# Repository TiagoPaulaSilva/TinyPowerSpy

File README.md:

# Tiny PowerSpy

Tiny PowerSpy is an IoT device, a smart plug for energy monitoring in wall outlets.

#### Compatible with: 
* [BitsTunnel](https://github.com/import-tiago/BitsTunnel)

## PCB Preview

## Enclosure Preview

## Schematic

### Contributing
0. Give this project a :star:
1. Create an issue and describe your idea.
2. [Fork it](https://github.com/import-tiago/TinyPowerSpy/fork).
3. Create your feature branch (`git checkout -b my-new-feature`).
4. Commit your changes (`git commit -a -m "Added feature title"`).
5. Publish the branch (`git push origin my-new-feature`).
6. Create a new pull request.
7. Done! :heavy_check_mark:

### License Information
<br /><span xmlns:dct="http://purl.org/dc/terms/" property="dct:title">Light's Thrill</span> by <a xmlns:cc="http://creativecommons.org/ns#" href="https://github.com/import-tiago" property="cc:attributionName" rel="cc:attributionURL">Tiago Silva</a> is licensed under a <a rel="license" href="http://creativecommons.org/licenses/by-sa/4.0/">Creative Commons Attribution-ShareAlike 4.0 International License</a>.<br />
Permissions beyond the scope of this license may be available at <a xmlns:cc="http://creativecommons.org/ns#" href="https://twitter.com/import_tiago" rel="cc:morePermissions">tiagodepaulasilva@gmail.com</a>.

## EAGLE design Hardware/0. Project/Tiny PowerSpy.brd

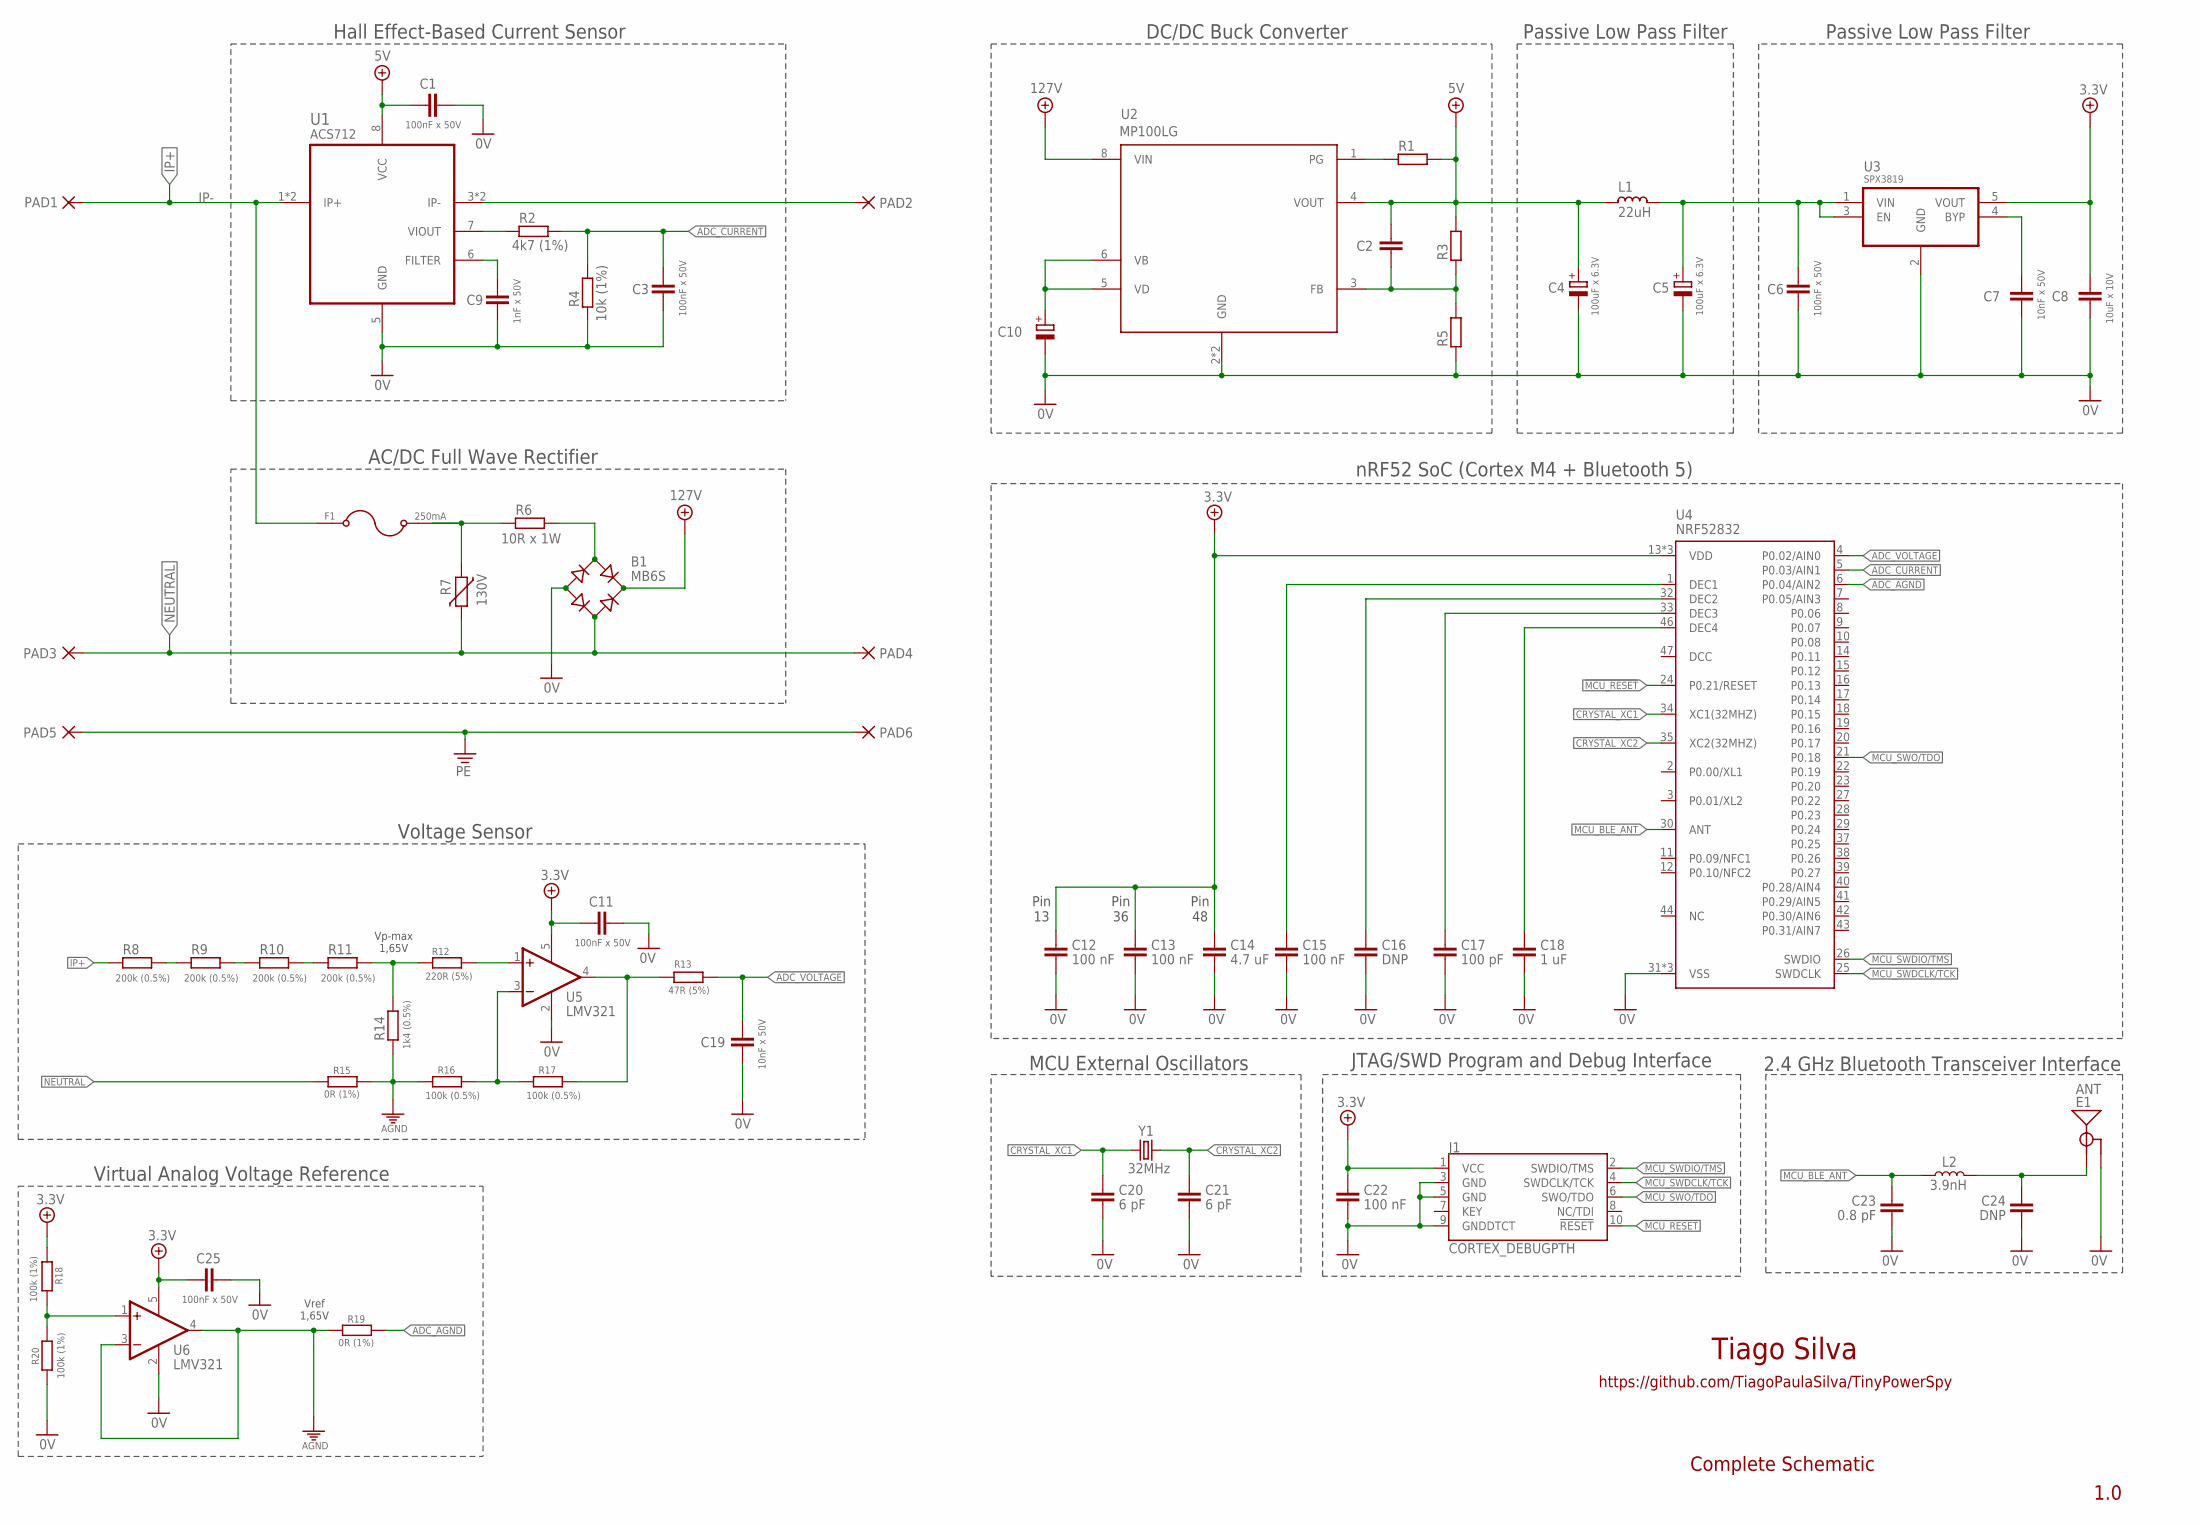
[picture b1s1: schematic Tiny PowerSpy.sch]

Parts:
B1: MB6S; SOIC-4
C1, C3, C6, C11, C25: 100nF x 50V; C0603
C2: C-EUC0603; C0603
C4, C5: 100uF x 6.3V; C1206K
C7, C19: 10nF x 50V; C0603
C8: 10uF x 10V; C0603
C9: 1nF x 50V; C0603
C10: CPOL-EUE3.5-8; E3,5-8
C12, C13, C15: 100 nF; C0402
C14: 4.7 uF; C0603
C16: DNP; C0402
C17: 100 pF; C0402
C18: 1 uF; C0603
C20, C21: 6 pF; C0402
C22: 100 nF; C0603
C23: 0.8 pF; C0603
C24: DNP; C0603
E1: ANT; TRACE_ANTENNA_2.4GHZ_15.2MM
F1: 250mA; FUSE_0154004.DR
J1: CORTEX_DEBUGPTH; 2X5-PTH-1.27MM
L1: 22uH; L0603
L2: 3.9nH; 0402
PAD1, PAD2, PAD4, PAD6: SMD5; SMD2,54-5,08
PAD3, PAD5: SMD2; SMD1,27-2,54
R1, R3, R5: R-EU_R0603; R0603
R2: 4k7 (1%); R0603
R4: 10k (1%); R0603
R6: 10R x 1W; 0207/5V
R7: 130V; S05K11
R8, R9, R10, R11: 200k (0.5%); R0603
R12: 220R (5%); R0603
R13: 47R (5%); R0603
R14: 1k4 (0.5%); R0603
R15, R19: 0R (1%); R0603
R16, R17: 100k (0.5%); R0603
R18, R20: 100k (1%); R0603
U1: ACS712; SOIC127P600X175-8N
U2: MP100LG; SOIC8E
U3: SPX3819; SOT95P280X145-5N
U4: NRF52832; QFN48-6X6MM
U5, U6: LMV321; SOT23-5
Y1: 32MHz; CRYSTAL-SMD-2.0X1.6MM

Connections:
0V: B1.-, C1.1, C3.2, C4.2, C5.2, C6.2, C7.2, C8.2, C9.2, C10.-, C11.1, C12.2, C13.2, C14.2, C15.2, C16.2, C17.2, C18.2, C19.2, C20.2, C21.2, C22.2, C23.2, C24.2, C25.2, E1.GND, J1.3 (GND), J1.5 (GND), J1.9 (GNDDTCT), R4.2, R5.1, R20.2, U1.5 (GND), U2.2 (GND), U2.9 (GND), U3.2 (GND), U4.31 (VSS), U4.45 (VSS), U4.EP (VSS), U5.2 (V-), U6.2 (V-)
3.3V: C8.1, C11.2, C12.1, C13.1, C14.1, C22.1, C25.1, J1.1 (VCC), R18.2, U3.5 (VOUT), U4.13 (VDD), U4.36 (VDD), U4.48 (VDD), U5.5 (V+), U6.5 (V+)
5V: C1.2, C2.1, C4.1, L1.2, R1.2, R3.2, U1.8 (VCC), U2.4 (VOUT)
127V: B1.+, U2.8 (VIN)
!MCU_RESET!: J1.10 (!RESET), U4.24 (P0.21/RESET)
ADC_AGND: R19.2, U4.6 (P0.04/AIN2)
ADC_CURRENT: C3.1, R2.2, R4.1, U4.5 (P0.03/AIN1)
ADC_VOLTAGE: C19.1, R13.1, U4.4 (P0.02/AIN0)
AGND: R14.2, R15.2, R16.2, R19.1, U6.3 (-IN), U6.4 (OUT)
CRYSTAL_XC1: C20.1, U4.34 (XC1(32MHZ)), Y1.3 (2)
CRYSTAL_XC2: C21.1, U4.35 (XC2(32MHZ)), Y1.1
IP+: F1.1, PAD1.1, R8.1, U1.1 (IP+), U1.2 (IP+)
IP-: PAD2.1, U1.3 (IP-), U1.4 (IP-)
MCU_BLE_ANT: C23.1, L2.2, U4.30 (ANT)
MCU_SWDCLK/TCK: J1.4 (SWDCLK/TCK), U4.25 (SWDCLK)
MCU_SWDIO/TMS: J1.2 (SWDIO/TMS), U4.26 (SWDIO)
MCU_SWO/TDO: J1.6 (SWO/TDO), U4.21 (P0.18)
unnamed: R1.1, U2.1 (PG)
unnamed: F1.2, R6.1, R7.1
unnamed: C16.1, U4.32 (DEC2)
unnamed: C2.2, R3.1, R5.2, U2.3 (FB)
unnamed: C10.+, U2.5 (VD), U2.6 (VB)
unnamed: C9.1, U1.6 (FILTER)
unnamed: B1.~1 (AC1), R6.2
unnamed: C15.1, U4.1 (DEC1)
unnamed: C18.1, U4.46 (DEC4)
unnamed: R2.1, U1.7 (VIOUT)
unnamed: C24.1, E1.ANT (SIGNAL), L2.1
unnamed: R9.2, R10.1
unnamed: C17.1, U4.33 (DEC3)
unnamed: R10.2, R11.1
unnamed: R13.2, R17.1, U5.4 (OUT)
unnamed: C5.1, C6.1, L1.1, U3.1 (VIN), U3.3 (EN)
unnamed: R8.2, R9.1
unnamed: C7.1, U3.4 (BYP)
unnamed: R16.1, R17.2, U5.3 (-IN)
unnamed: R11.2, R12.2, R14.1
unnamed: R12.1, U5.1 (+IN)
unnamed: R18.1, R20.1, U6.1 (+IN)
NEUTRAL: B1.~2 (AC2), PAD3.1, PAD4.1, R7.2, R15.1
PE: PAD5.1, PAD6.1

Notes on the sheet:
Tiago Silva
https://github.com/TiagoPaulaSilva/TinyPowerSpy
1.0
Complete Schematic
Vp-max 1,65V
Vref 1,65V
Pin 13
Pin 36
Pin 48
JTAG/SWD Program and Debug Interface
nRF52 SoC (Cortex M4 + Bluetooth 5)
MCU External Oscillators
2.4 GHz Bluetooth Transceiver Interface
DC/DC Buck Converter
Passive Low Pass Filter
AC/DC Full Wave Rectifier
Hall Effect-Based Current Sensor
Virtual Analog Voltage Reference
Voltage Sensor

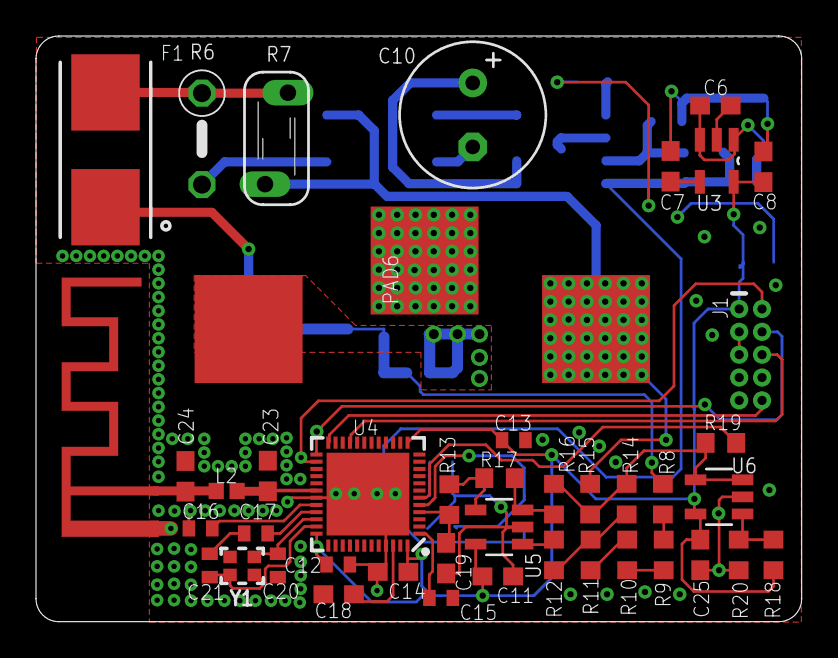
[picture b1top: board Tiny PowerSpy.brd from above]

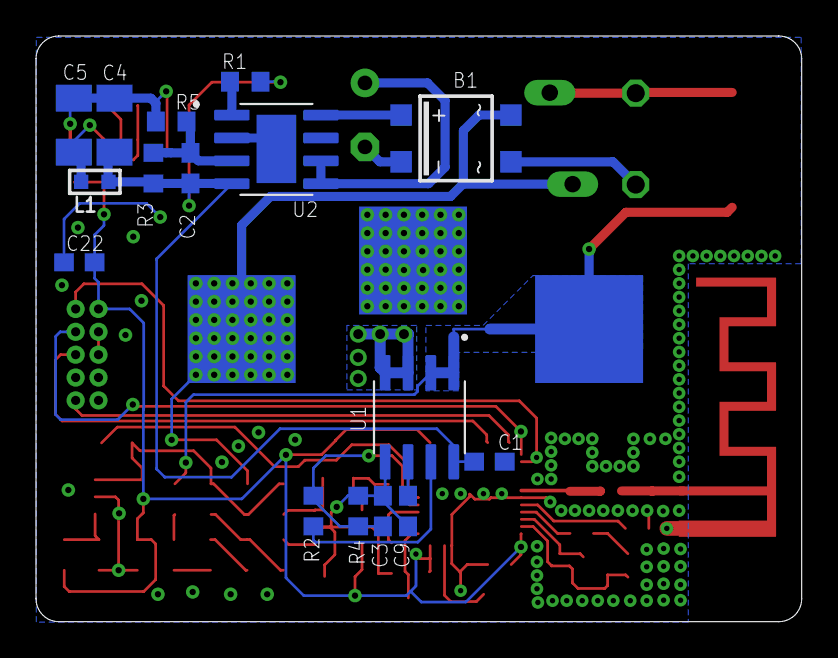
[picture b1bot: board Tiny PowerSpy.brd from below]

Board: 2 copper layers, 42.5 x 32.5 mm, 64 parts (19 on the bottom side), 41 nets.

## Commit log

2020-07-23 WIP - Schematic 1.0
2020-07-23 Read-me added
2020-07-23 Enclosure preview added
2020-07-23 Datasheet added
2020-07-26 Minor improvement
2020-07-26 PCB 1.0 - WIP
2020-07-26 DC-DC buck IC added
2020-07-27 PCB 1.0 - Done
2020-07-27 Gerber files from 1.0 project added
2020-07-27 Schematic preview added
2020-07-27 Minor improvements
2020-07-27 PCB Preview added
2020-07-27 improved image added
2023-07-21 usernames in URLs updated

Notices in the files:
parts and their libraries:
rc-master-smd: Copyright (C) 2007, Bob Starr
SparkFun-Connectors: Licensing: Creative Commons ShareAlike 4.0 International - https://creativecommons.org/licenses/by-sa/4.0
